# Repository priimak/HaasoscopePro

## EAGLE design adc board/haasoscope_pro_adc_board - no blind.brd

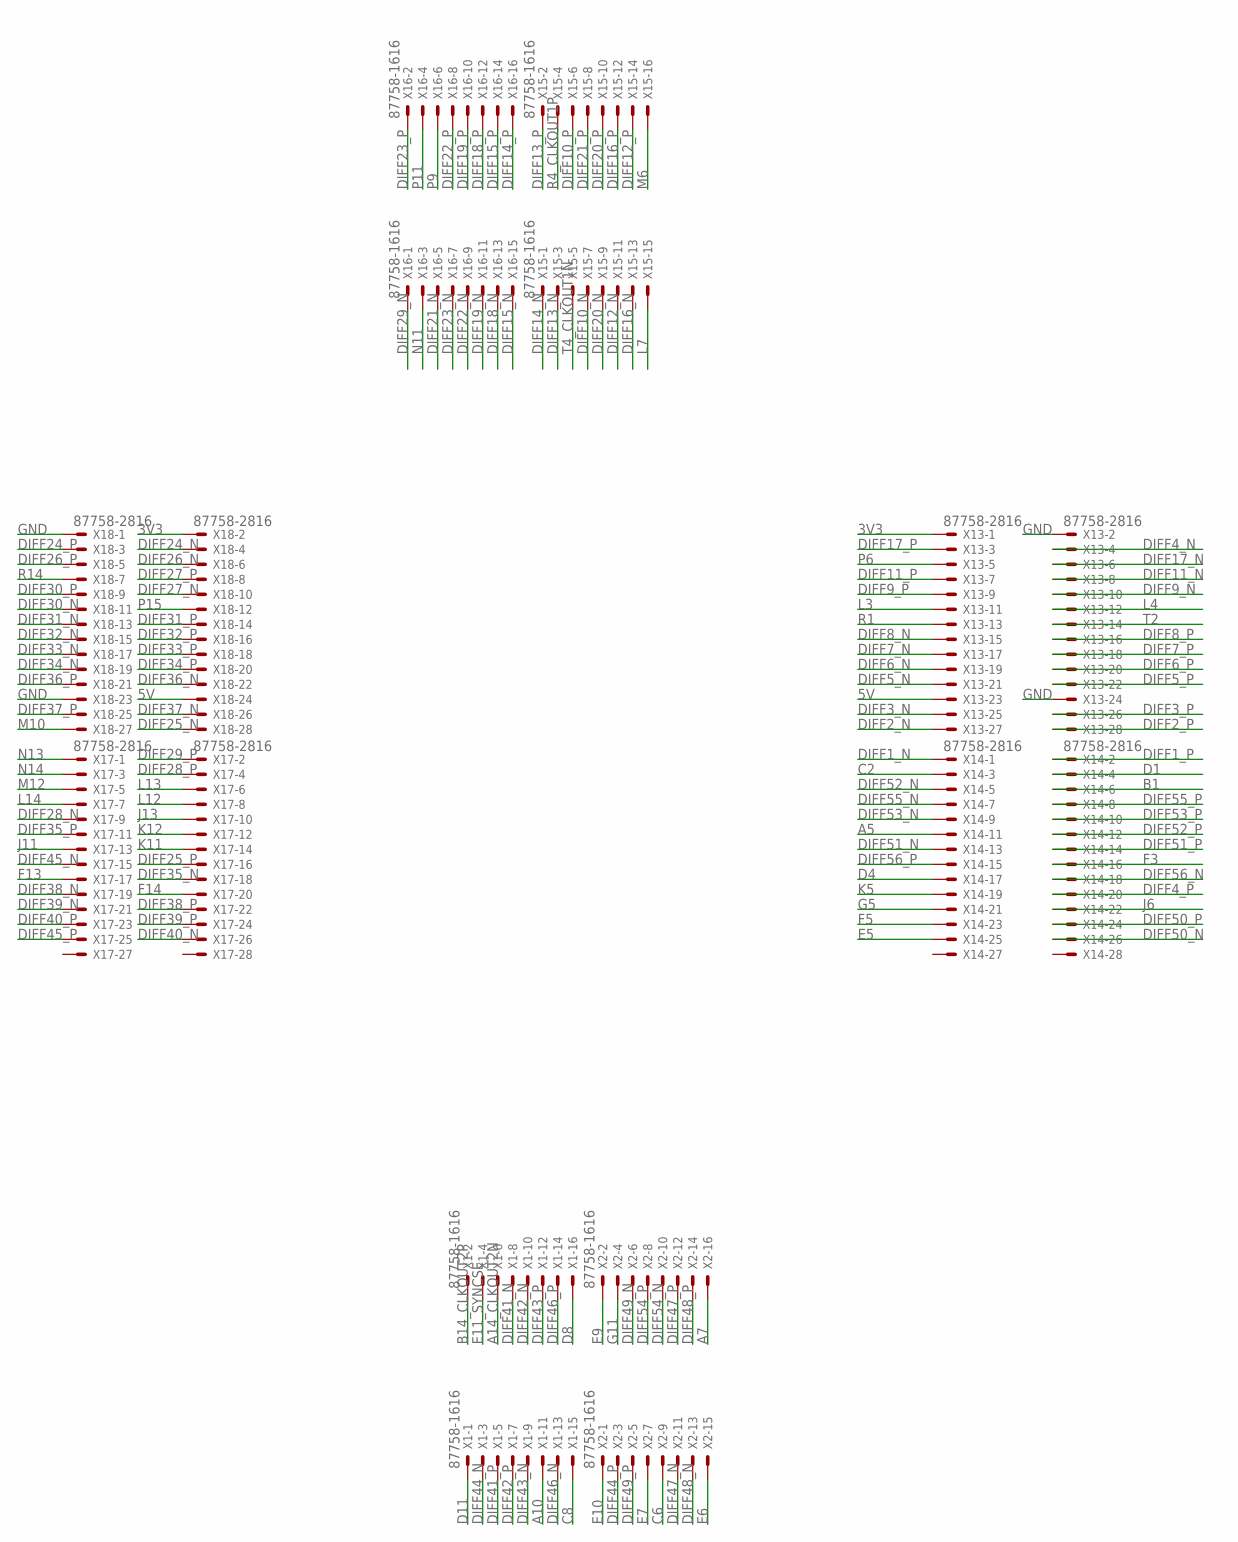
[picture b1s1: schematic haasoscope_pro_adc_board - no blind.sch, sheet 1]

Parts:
X1, X2, X15, X16: 87758-1616
X13, X14, X17, X18: 87758-2816

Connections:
3V3: X13.1, X18.2; also elsewhere on the board
5V: X13.23, X18.24; also elsewhere on the board
A5: X14.11; also elsewhere on the board
A7: X2.16; also elsewhere on the board
A10: X1.11; also elsewhere on the board
A14_CLKOUT2N: X1.6; also elsewhere on the board
B1: X14.6; also elsewhere on the board
B14_CLKOUT2P: X1.2; also elsewhere on the board
C2: X14.3; also elsewhere on the board
C6: X2.9; also elsewhere on the board
C8: X1.15; also elsewhere on the board
D1: X14.4; also elsewhere on the board
D4: X14.17; also elsewhere on the board
D8: X1.16; also elsewhere on the board
D11: X1.1; also elsewhere on the board
DIFF1_N: X14.1; also elsewhere on the board
DIFF1_P: X14.2; also elsewhere on the board
DIFF2_N: X13.27; also elsewhere on the board
DIFF2_P: X13.28; also elsewhere on the board
DIFF3_N: X13.25; also elsewhere on the board
DIFF3_P: X13.26; also elsewhere on the board
DIFF4_N: X13.4; also elsewhere on the board
DIFF4_P: X14.20; also elsewhere on the board
DIFF5_N: X13.21; also elsewhere on the board
DIFF5_P: X13.22; also elsewhere on the board
DIFF6_N: X13.19; also elsewhere on the board
DIFF6_P: X13.20; also elsewhere on the board
DIFF7_N: X13.17; also elsewhere on the board
DIFF7_P: X13.18; also elsewhere on the board
DIFF8_N: X13.15; also elsewhere on the board
DIFF8_P: X13.16; also elsewhere on the board
DIFF9_N: X13.10; also elsewhere on the board
DIFF9_P: X13.9; also elsewhere on the board
DIFF10_N: X15.7; also elsewhere on the board
DIFF10_P: X15.6; also elsewhere on the board
DIFF11_N: X13.8; also elsewhere on the board
DIFF11_P: X13.7; also elsewhere on the board
DIFF12_N: X15.11; also elsewhere on the board
DIFF12_P: X15.14; also elsewhere on the board
DIFF13_N: X15.3; also elsewhere on the board
DIFF13_P: X15.2; also elsewhere on the board
DIFF14_N: X15.1; also elsewhere on the board
DIFF14_P: X16.16; also elsewhere on the board
DIFF15_N: X16.15; also elsewhere on the board
DIFF15_P: X16.14; also elsewhere on the board
DIFF16_N: X15.13; also elsewhere on the board
DIFF16_P: X15.12; also elsewhere on the board
DIFF17_N: X13.6; also elsewhere on the board
DIFF17_P: X13.3; also elsewhere on the board
DIFF18_N: X16.13; also elsewhere on the board
DIFF18_P: X16.12; also elsewhere on the board
DIFF19_N: X16.11; also elsewhere on the board
DIFF19_P: X16.10; also elsewhere on the board
DIFF20_N: X15.9; also elsewhere on the board
DIFF20_P: X15.10; also elsewhere on the board
DIFF21_N: X16.5; also elsewhere on the board
DIFF21_P: X15.8; also elsewhere on the board
DIFF22_N: X16.9; also elsewhere on the board
DIFF22_P: X16.8; also elsewhere on the board
DIFF23_N: X16.7; also elsewhere on the board
DIFF23_P: X16.2; also elsewhere on the board
DIFF24_N: X18.4; also elsewhere on the board
DIFF24_P: X18.3; also elsewhere on the board
DIFF25_N: X18.28; also elsewhere on the board
DIFF25_P: X17.16; also elsewhere on the board
DIFF26_N: X18.6; also elsewhere on the board
DIFF26_P: X18.5; also elsewhere on the board
DIFF27_N: X18.10; also elsewhere on the board
DIFF27_P: X18.8; also elsewhere on the board
DIFF28_N: X17.9; also elsewhere on the board
DIFF28_P: X17.4; also elsewhere on the board
DIFF29_N: X16.1; also elsewhere on the board
DIFF29_P: X17.2; also elsewhere on the board
DIFF30_N: X18.11; also elsewhere on the board
DIFF30_P: X18.9; also elsewhere on the board
DIFF31_N: X18.13; also elsewhere on the board
DIFF31_P: X18.14; also elsewhere on the board
DIFF32_N: X18.15; also elsewhere on the board
DIFF32_P: X18.16; also elsewhere on the board
DIFF33_N: X18.17; also elsewhere on the board
DIFF33_P: X18.18; also elsewhere on the board
DIFF34_N: X18.19; also elsewhere on the board
DIFF34_P: X18.20; also elsewhere on the board
DIFF35_N: X17.18; also elsewhere on the board
DIFF35_P: X17.11; also elsewhere on the board
DIFF36_N: X18.22; also elsewhere on the board
DIFF36_P: X18.21; also elsewhere on the board
DIFF37_N: X18.26; also elsewhere on the board
DIFF37_P: X18.25; also elsewhere on the board
DIFF38_N: X17.19; also elsewhere on the board
DIFF38_P: X17.22; also elsewhere on the board
DIFF39_N: X17.21; also elsewhere on the board
DIFF39_P: X17.24; also elsewhere on the board
DIFF40_N: X17.26; also elsewhere on the board
DIFF40_P: X17.23; also elsewhere on the board
DIFF41_N: X1.8; also elsewhere on the board
DIFF41_P: X1.5; also elsewhere on the board
DIFF42_N: X1.10; also elsewhere on the board
DIFF42_P: X1.7; also elsewhere on the board
DIFF43_N: X1.9; also elsewhere on the board
DIFF43_P: X1.12; also elsewhere on the board
DIFF44_N: X1.3; also elsewhere on the board
DIFF44_P: X2.3; also elsewhere on the board
DIFF45_N: X17.15; also elsewhere on the board
DIFF45_P: X17.25; also elsewhere on the board
DIFF46_N: X1.13; also elsewhere on the board
DIFF46_P: X1.14; also elsewhere on the board
DIFF47_N: X2.11; also elsewhere on the board
DIFF47_P: X2.12; also elsewhere on the board
DIFF48_N: X2.13; also elsewhere on the board
DIFF48_P: X2.14; also elsewhere on the board
DIFF49_N: X2.6; also elsewhere on the board
DIFF49_P: X2.5; also elsewhere on the board
DIFF50_N: X14.26; also elsewhere on the board
DIFF50_P: X14.24; also elsewhere on the board
DIFF51_N: X14.13; also elsewhere on the board
DIFF51_P: X14.14; also elsewhere on the board
DIFF52_N: X14.5; also elsewhere on the board
DIFF52_P: X14.12; also elsewhere on the board
DIFF53_N: X14.9; also elsewhere on the board
DIFF53_P: X14.10; also elsewhere on the board
DIFF54_N: X2.10; also elsewhere on the board
DIFF54_P: X2.8; also elsewhere on the board
DIFF55_N: X14.7; also elsewhere on the board
DIFF55_P: X14.8; also elsewhere on the board
DIFF56_N: X14.18; also elsewhere on the board
DIFF56_P: X14.15; also elsewhere on the board
E5: X14.25; also elsewhere on the board
E6: X2.15; also elsewhere on the board
E7: X2.7; also elsewhere on the board
E9: X2.2; also elsewhere on the board
E10: X2.1; also elsewhere on the board
E11_SYNCSE: X1.4; also elsewhere on the board
F3: X14.16; also elsewhere on the board
F5: X14.23; also elsewhere on the board
F13: X17.17; also elsewhere on the board
F14: X17.20; also elsewhere on the board
G5: X14.21; also elsewhere on the board
G11: X2.4; also elsewhere on the board
GND: X13.2, X13.24, X18.1, X18.23; also elsewhere on the board
J6: X14.22; also elsewhere on the board
J11: X17.13; also elsewhere on the board
J13: X17.10; also elsewhere on the board
K5: X14.19; also elsewhere on the board
K11: X17.14; also elsewhere on the board
K12: X17.12; also elsewhere on the board
L3: X13.11; also elsewhere on the board
L4: X13.12; also elsewhere on the board
L7: X15.15; also elsewhere on the board
L12: X17.8; also elsewhere on the board
L13: X17.6; also elsewhere on the board
L14: X17.7; also elsewhere on the board
M6: X15.16; also elsewhere on the board
M10: X18.27; also elsewhere on the board
M12: X17.5; also elsewhere on the board
N11: X16.3; also elsewhere on the board
N13: X17.1; also elsewhere on the board
N14: X17.3; also elsewhere on the board
P6: X13.5; also elsewhere on the board
P9: X16.6; also elsewhere on the board
P11: X16.4; also elsewhere on the board
P15: X18.12; also elsewhere on the board
R1: X13.13; also elsewhere on the board
R4_CLKOUT1P: X15.4; also elsewhere on the board
R14: X18.7; also elsewhere on the board
T2: X13.14; also elsewhere on the board
T4_CLKOUT1N: X15.5; also elsewhere on the board

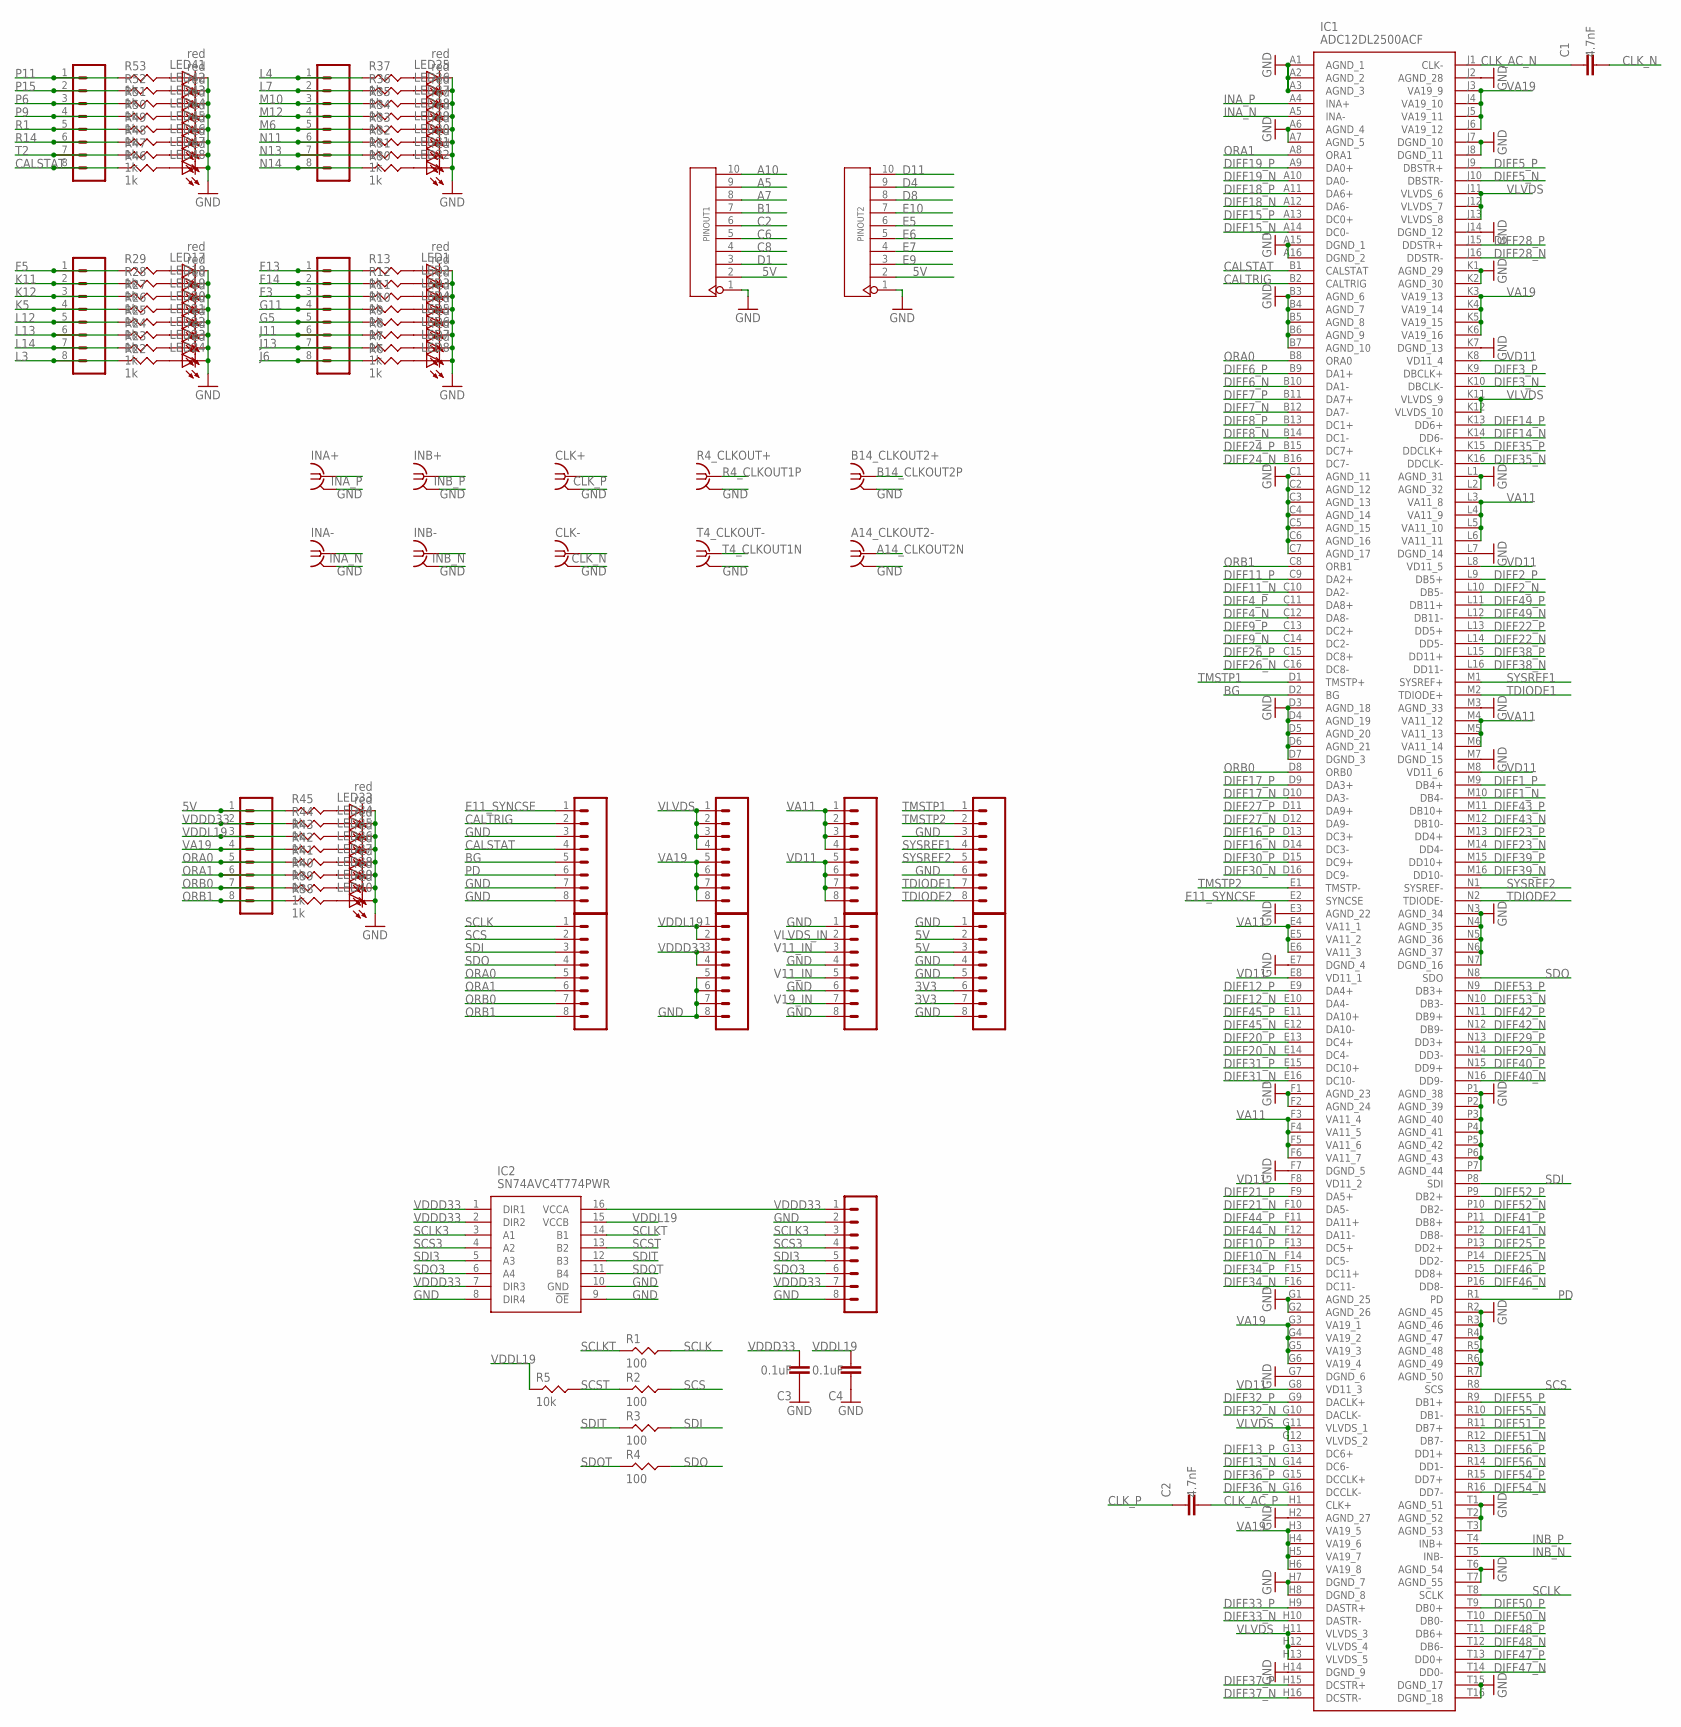
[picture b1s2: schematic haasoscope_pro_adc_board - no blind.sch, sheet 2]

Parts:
A14_CLKOUT2-: BU-SMB-V
B14_CLKOUT2+: BU-SMB-V
C1, C2: 4.7nF; RESC0402_N
C3, C4: 0.1uF; RESC0402_N
CLK+: BU-SMB-V
CLK-: BU-SMB-V
IC1: ADC12DL2500ACF; BGA256C100P16X16_1700X1700X331; MANUFACTURER_PART_NUMBER ADC12DL500ACF
IC2: SN74AVC4T774PWR; SOP65P640X120-16N
INA+: BU-SMB-V
INA-: BU-SMB-V
INB+: BU-SMB-V
INB-: BU-SMB-V
J1, J2, J3, J4, J5, J6, J7, J8, J10, J11, J12, J13, J16, J17: 8pin; 1X08
LED1, LED2, LED3, LED4, LED5, LED6, LED7, LED8, LED17, LED18, LED19, LED20, LED21, LED22, LED23, LED24, LED25, LED26, LED27, LED28, LED29, LED30, LED31, LED32, LED33, LED34, LED35, LED36, LED37, LED38, LED39, LED40, LED41, LED42, LED43, LED44, LED45, LED46, LED47, LED48: red; CHIP-LED0603
PINOUT1, PINOUT2: YELLOW-10P-2.54; H10-2.54
R1, R2, R3, R4: 100; RES-0402
R4_CLKOUT+: BU-SMB-V
R5: 10k; RES-0402
R6, R7, R8, R9, R10, R11, R12, R13, R22, R23, R24, R25, R26, R27, R28, R29, R30, R31, R32, R33, R34, R35, R36, R37, R38, R39, R40, R41, R42, R43, R44, R45, R46, R47, R48, R49, R50, R51, R52, R53: 1k; RES-0402
T4_CLKOUT-: BU-SMB-V

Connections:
3V3: J6.6, J6.7; also elsewhere on the board
5V: J6.2, J6.3, J12.1, PINOUT1.2, PINOUT2.2, R45.P$1; also elsewhere on the board
A5: PINOUT1.9; also elsewhere on the board
A7: PINOUT1.8; also elsewhere on the board
A10: PINOUT1.10; also elsewhere on the board
A14_CLKOUT2N: A14_CLKOUT2-.1; also elsewhere on the board
B1: PINOUT1.7; also elsewhere on the board
B14_CLKOUT2P: B14_CLKOUT2+.1; also elsewhere on the board
BG: IC1.D2 (BG), J17.5
C2: PINOUT1.6; also elsewhere on the board
C6: PINOUT1.5; also elsewhere on the board
C8: PINOUT1.4; also elsewhere on the board
CALSTAT: IC1.B1 (CALSTAT), J13.8, J17.4, R46.P$1
CALTRIG: IC1.B2 (CALTRIG), J17.2
CLK_AC_N: C1.1, IC1.J1 (CLK-)
CLK_AC_P: C2.2, IC1.H1 (CLK+)
CLK_N: C1.2, CLK-.1
CLK_P: C2.1, CLK+.1
D1: PINOUT1.3; also elsewhere on the board
D4: PINOUT2.9; also elsewhere on the board
D8: PINOUT2.8; also elsewhere on the board
D11: PINOUT2.10; also elsewhere on the board
DIFF1_N: IC1.M10 (DB4-); also elsewhere on the board
DIFF1_P: IC1.M9 (DB4+); also elsewhere on the board
DIFF2_N: IC1.L10 (DB5-); also elsewhere on the board
DIFF2_P: IC1.L9 (DB5+); also elsewhere on the board
DIFF3_N: IC1.K10 (DBCLK-); also elsewhere on the board
DIFF3_P: IC1.K9 (DBCLK+); also elsewhere on the board
DIFF4_N: IC1.C12 (DA8-); also elsewhere on the board
DIFF4_P: IC1.C11 (DA8+); also elsewhere on the board
DIFF5_N: IC1.J10 (DBSTR-); also elsewhere on the board
DIFF5_P: IC1.J9 (DBSTR+); also elsewhere on the board
DIFF6_N: IC1.B10 (DA1-); also elsewhere on the board
DIFF6_P: IC1.B9 (DA1+); also elsewhere on the board
DIFF7_N: IC1.B12 (DA7-); also elsewhere on the board
DIFF7_P: IC1.B11 (DA7+); also elsewhere on the board
DIFF8_N: IC1.B14 (DC1-); also elsewhere on the board
DIFF8_P: IC1.B13 (DC1+); also elsewhere on the board
DIFF9_N: IC1.C14 (DC2-); also elsewhere on the board
DIFF9_P: IC1.C13 (DC2+); also elsewhere on the board
DIFF10_N: IC1.F14 (DC5-); also elsewhere on the board
DIFF10_P: IC1.F13 (DC5+); also elsewhere on the board
DIFF11_N: IC1.C10 (DA2-); also elsewhere on the board
DIFF11_P: IC1.C9 (DA2+); also elsewhere on the board
DIFF12_N: IC1.E10 (DA4-); also elsewhere on the board
DIFF12_P: IC1.E9 (DA4+); also elsewhere on the board
DIFF13_N: IC1.G14 (DC6-); also elsewhere on the board
DIFF13_P: IC1.G13 (DC6+); also elsewhere on the board
DIFF14_N: IC1.K14 (DD6-); also elsewhere on the board
DIFF14_P: IC1.K13 (DD6+); also elsewhere on the board
DIFF15_N: IC1.A14 (DC0-); also elsewhere on the board
DIFF15_P: IC1.A13 (DC0+); also elsewhere on the board
DIFF16_N: IC1.D14 (DC3-); also elsewhere on the board
DIFF16_P: IC1.D13 (DC3+); also elsewhere on the board
DIFF17_N: IC1.D10 (DA3-); also elsewhere on the board
DIFF17_P: IC1.D9 (DA3+); also elsewhere on the board
DIFF18_N: IC1.A12 (DA6-); also elsewhere on the board
DIFF18_P: IC1.A11 (DA6+); also elsewhere on the board
DIFF19_N: IC1.A10 (DA0-); also elsewhere on the board
DIFF19_P: IC1.A9 (DA0+); also elsewhere on the board
DIFF20_N: IC1.E14 (DC4-); also elsewhere on the board
DIFF20_P: IC1.E13 (DC4+); also elsewhere on the board
DIFF21_N: IC1.F10 (DA5-); also elsewhere on the board
DIFF21_P: IC1.F9 (DA5+); also elsewhere on the board
DIFF22_N: IC1.L14 (DD5-); also elsewhere on the board
DIFF22_P: IC1.L13 (DD5+); also elsewhere on the board
DIFF23_N: IC1.M14 (DD4-); also elsewhere on the board
DIFF23_P: IC1.M13 (DD4+); also elsewhere on the board
DIFF24_N: IC1.B16 (DC7-); also elsewhere on the board
DIFF24_P: IC1.B15 (DC7+); also elsewhere on the board
DIFF25_N: IC1.P14 (DD2-); also elsewhere on the board
DIFF25_P: IC1.P13 (DD2+); also elsewhere on the board
DIFF26_N: IC1.C16 (DC8-); also elsewhere on the board
DIFF26_P: IC1.C15 (DC8+); also elsewhere on the board
DIFF27_N: IC1.D12 (DA9-); also elsewhere on the board
DIFF27_P: IC1.D11 (DA9+); also elsewhere on the board
DIFF28_N: IC1.J16 (DDSTR-); also elsewhere on the board
DIFF28_P: IC1.J15 (DDSTR+); also elsewhere on the board
DIFF29_N: IC1.N14 (DD3-); also elsewhere on the board
DIFF29_P: IC1.N13 (DD3+); also elsewhere on the board
DIFF30_N: IC1.D16 (DC9-); also elsewhere on the board
DIFF30_P: IC1.D15 (DC9+); also elsewhere on the board
DIFF31_N: IC1.E16 (DC10-); also elsewhere on the board
DIFF31_P: IC1.E15 (DC10+); also elsewhere on the board
DIFF32_N: IC1.G10 (DACLK-); also elsewhere on the board
DIFF32_P: IC1.G9 (DACLK+); also elsewhere on the board
DIFF33_N: IC1.H10 (DASTR-); also elsewhere on the board
DIFF33_P: IC1.H9 (DASTR+); also elsewhere on the board
DIFF34_N: IC1.F16 (DC11-); also elsewhere on the board
DIFF34_P: IC1.F15 (DC11+); also elsewhere on the board
DIFF35_N: IC1.K16 (DDCLK-); also elsewhere on the board
DIFF35_P: IC1.K15 (DDCLK+); also elsewhere on the board
DIFF36_N: IC1.G16 (DCCLK-); also elsewhere on the board
DIFF36_P: IC1.G15 (DCCLK+); also elsewhere on the board
DIFF37_N: IC1.H16 (DCSTR-); also elsewhere on the board
DIFF37_P: IC1.H15 (DCSTR+); also elsewhere on the board
DIFF38_N: IC1.L16 (DD11-); also elsewhere on the board
DIFF38_P: IC1.L15 (DD11+); also elsewhere on the board
DIFF39_N: IC1.M16 (DD10-); also elsewhere on the board
DIFF39_P: IC1.M15 (DD10+); also elsewhere on the board
DIFF40_N: IC1.N16 (DD9-); also elsewhere on the board
DIFF40_P: IC1.N15 (DD9+); also elsewhere on the board
DIFF41_N: IC1.P12 (DB8-); also elsewhere on the board
DIFF41_P: IC1.P11 (DB8+); also elsewhere on the board
DIFF42_N: IC1.N12 (DB9-); also elsewhere on the board
DIFF42_P: IC1.N11 (DB9+); also elsewhere on the board
DIFF43_N: IC1.M12 (DB10-); also elsewhere on the board
DIFF43_P: IC1.M11 (DB10+); also elsewhere on the board
DIFF44_N: IC1.F12 (DA11-); also elsewhere on the board
DIFF44_P: IC1.F11 (DA11+); also elsewhere on the board
DIFF45_N: IC1.E12 (DA10-); also elsewhere on the board
DIFF45_P: IC1.E11 (DA10+); also elsewhere on the board
DIFF46_N: IC1.P16 (DD8-); also elsewhere on the board
DIFF46_P: IC1.P15 (DD8+); also elsewhere on the board
DIFF47_N: IC1.T14 (DD0-); also elsewhere on the board
DIFF47_P: IC1.T13 (DD0+); also elsewhere on the board
DIFF48_N: IC1.T12 (DB6-); also elsewhere on the board
DIFF48_P: IC1.T11 (DB6+); also elsewhere on the board
DIFF49_N: IC1.L12 (DB11-); also elsewhere on the board
DIFF49_P: IC1.L11 (DB11+); also elsewhere on the board
DIFF50_N: IC1.T10 (DB0-); also elsewhere on the board
DIFF50_P: IC1.T9 (DB0+); also elsewhere on the board
DIFF51_N: IC1.R12 (DB7-); also elsewhere on the board
DIFF51_P: IC1.R11 (DB7+); also elsewhere on the board
DIFF52_N: IC1.P10 (DB2-); also elsewhere on the board
DIFF52_P: IC1.P9 (DB2+); also elsewhere on the board
DIFF53_N: IC1.N10 (DB3-); also elsewhere on the board
DIFF53_P: IC1.N9 (DB3+); also elsewhere on the board
DIFF54_N: IC1.R16 (DD7-); also elsewhere on the board
DIFF54_P: IC1.R15 (DD7+); also elsewhere on the board
DIFF55_N: IC1.R10 (DB1-); also elsewhere on the board
DIFF55_P: IC1.R9 (DB1+); also elsewhere on the board
DIFF56_N: IC1.R14 (DD1-); also elsewhere on the board
DIFF56_P: IC1.R13 (DD1+); also elsewhere on the board
E5: PINOUT2.6; also elsewhere on the board
E6: PINOUT2.5; also elsewhere on the board
E7: PINOUT2.4; also elsewhere on the board
E9: PINOUT2.3; also elsewhere on the board
E10: PINOUT2.7; also elsewhere on the board
E11_SYNCSE: IC1.E2 (SYNCSE), J17.1; also elsewhere on the board
F3: J8.3, R11.P$1; also elsewhere on the board
F5: J10.1, R29.P$1; also elsewhere on the board
F13: J8.1, R13.P$1; also elsewhere on the board
F14: J8.2, R12.P$1; also elsewhere on the board
G5: J8.5, R9.P$1; also elsewhere on the board
G11: J8.4, R10.P$1; also elsewhere on the board
GND: A14_CLKOUT2-.2, A14_CLKOUT2-.3 (2), A14_CLKOUT2-.4 (2), A14_CLKOUT2-.5 (2), B14_CLKOUT2+.2, B14_CLKOUT2+.3 (2), B14_CLKOUT2+.4 (2), B14_CLKOUT2+.5 (2), C3.1, C4.1, CLK+.2, CLK+.3 (2), CLK+.4 (2), CLK+.5 (2), CLK-.2, CLK-.3 (2), CLK-.4 (2), CLK-.5 (2), IC1.A1 (AGND_1), IC1.A2 (AGND_2), IC1.A3 (AGND_3), IC1.A6 (AGND_4), IC1.A7 (AGND_5), IC1.A15 (DGND_1), IC1.A16 (DGND_2), IC1.B3 (AGND_6), IC1.B4 (AGND_7), IC1.B5 (AGND_8), IC1.B6 (AGND_9), IC1.B7 (AGND_10), IC1.C1 (AGND_11), IC1.C2 (AGND_12), IC1.C3 (AGND_13), IC1.C4 (AGND_14), IC1.C5 (AGND_15), IC1.C6 (AGND_16), IC1.C7 (AGND_17), IC1.D3 (AGND_18), IC1.D4 (AGND_19), IC1.D5 (AGND_20), IC1.D6 (AGND_21), IC1.D7 (DGND_3), IC1.E3 (AGND_22), IC1.E7 (DGND_4), IC1.F1 (AGND_23), IC1.F2 (AGND_24), IC1.F7 (DGND_5), IC1.G1 (AGND_25), IC1.G2 (AGND_26), IC1.G7 (DGND_6), IC1.H2 (AGND_27), IC1.H7 (DGND_7), IC1.H8 (DGND_8), IC1.H14 (DGND_9), IC1.J2 (AGND_28), IC1.J7 (DGND_10), IC1.J8 (DGND_11), IC1.J14 (DGND_12), IC1.K1 (AGND_29), IC1.K2 (AGND_30), IC1.K7 (DGND_13), IC1.L1 (AGND_31), IC1.L2 (AGND_32), IC1.L7 (DGND_14), IC1.M3 (AGND_33), IC1.M7 (DGND_15), IC1.N3 (AGND_34), IC1.N4 (AGND_35), IC1.N5 (AGND_36), IC1.N6 (AGND_37), IC1.N7 (DGND_16), IC1.P1 (AGND_38), IC1.P2 (AGND_39), IC1.P3 (AGND_40), IC1.P4 (AGND_41), IC1.P5 (AGND_42), IC1.P6 (AGND_43), IC1.P7 (AGND_44), IC1.R2 (AGND_45), IC1.R3 (AGND_46), IC1.R4 (AGND_47), IC1.R5 (AGND_48), IC1.R6 (AGND_49), IC1.R7 (AGND_50), IC1.T1 (AGND_51), IC1.T2 (AGND_52), IC1.T3 (AGND_53), IC1.T6 (AGND_54), IC1.T7 (AGND_55), IC1.T15 (DGND_17), IC1.T16 (DGND_18), IC2.8 (DIR4), IC2.9 (!OE), IC2.10 (GND), INA+.2, INA+.3 (2), INA+.4 (2), INA+.5 (2), INA-.2, INA-.3 (2), INA-.4 (2), INA-.5 (2), INB+.2, INB+.3 (2), INB+.4 (2), INB+.5 (2), INB-.2, INB-.3 (2), INB-.4 (2), INB-.5 (2), J2.5, J2.6, J2.7, J2.8, J4.2, J4.8, J5.1, J5.4, J5.6, J5.8, J6.1, J6.4, J6.5, J6.8, J7.3, J7.6, J17.3, J17.7, J17.8, LED1.C, LED2.C, LED3.C, LED4.C, LED5.C, LED6.C, LED7.C, LED8.C, LED17.C, LED18.C, LED19.C, LED20.C, LED21.C, LED22.C, LED23.C, LED24.C, LED25.C, LED26.C, LED27.C, LED28.C, LED29.C, LED30.C, LED31.C, LED32.C, LED33.C, LED34.C, LED35.C, LED36.C, LED37.C, LED38.C, LED39.C, LED40.C, LED41.C, LED42.C, LED43.C, LED44.C, LED45.C, LED46.C, LED47.C, LED48.C, PINOUT1.1, PINOUT2.1, R4_CLKOUT+.2, R4_CLKOUT+.3 (2), R4_CLKOUT+.4 (2), R4_CLKOUT+.5 (2), T4_CLKOUT-.2, T4_CLKOUT-.3 (2), T4_CLKOUT-.4 (2), T4_CLKOUT-.5 (2); also elsewhere on the board
INA_N: IC1.A5 (INA-), INA-.1
INA_P: IC1.A4 (INA+), INA+.1
INB_N: IC1.T5 (INB-), INB-.1
INB_P: IC1.T4 (INB+), INB+.1
J6: J8.8, R6.P$1; also elsewhere on the board
J11: J8.6, R8.P$1; also elsewhere on the board
J13: J8.7, R7.P$1; also elsewhere on the board
K5: J10.4, R26.P$1; also elsewhere on the board
K11: J10.2, R28.P$1; also elsewhere on the board
K12: J10.3, R27.P$1; also elsewhere on the board
L3: J10.8, R22.P$1; also elsewhere on the board
L4: J11.1, R37.P$1; also elsewhere on the board
L7: J11.2, R36.P$1; also elsewhere on the board
L12: J10.5, R25.P$1; also elsewhere on the board
L13: J10.6, R24.P$1; also elsewhere on the board
L14: J10.7, R23.P$1; also elsewhere on the board
M6: J11.5, R33.P$1; also elsewhere on the board
M10: J11.3, R35.P$1; also elsewhere on the board
M12: J11.4, R34.P$1; also elsewhere on the board
N11: J11.6, R32.P$1; also elsewhere on the board
N13: J11.7, R31.P$1; also elsewhere on the board
N14: J11.8, R30.P$1; also elsewhere on the board
unnamed: LED1.A, R13.P$2
unnamed: LED2.A, R12.P$2
unnamed: LED3.A, R11.P$2
unnamed: LED4.A, R10.P$2
unnamed: LED5.A, R9.P$2
unnamed: LED6.A, R8.P$2
unnamed: LED7.A, R7.P$2
unnamed: LED8.A, R6.P$2
unnamed: LED17.A, R29.P$2
unnamed: LED18.A, R28.P$2
unnamed: LED19.A, R27.P$2
unnamed: LED20.A, R26.P$2
unnamed: LED21.A, R25.P$2
unnamed: LED22.A, R24.P$2
unnamed: LED23.A, R23.P$2
unnamed: LED24.A, R22.P$2
unnamed: LED25.A, R37.P$2
unnamed: LED26.A, R36.P$2
unnamed: LED27.A, R35.P$2
unnamed: LED28.A, R34.P$2
unnamed: LED29.A, R33.P$2
unnamed: LED30.A, R32.P$2
unnamed: LED31.A, R31.P$2
unnamed: LED32.A, R30.P$2
unnamed: LED33.A, R45.P$2
unnamed: LED34.A, R44.P$2
unnamed: LED35.A, R43.P$2
unnamed: LED36.A, R42.P$2
unnamed: LED37.A, R41.P$2
unnamed: LED38.A, R40.P$2
unnamed: LED39.A, R39.P$2
unnamed: LED40.A, R38.P$2
unnamed: LED41.A, R53.P$2
unnamed: LED42.A, R52.P$2
unnamed: LED43.A, R51.P$2
unnamed: LED44.A, R50.P$2
unnamed: LED45.A, R49.P$2
unnamed: LED46.A, R48.P$2
unnamed: LED47.A, R47.P$2
unnamed: LED48.A, R46.P$2
ORA0: IC1.B8 (ORA0), J12.5, J16.5, R41.P$1
ORA1: IC1.A8 (ORA1), J12.6, J16.6, R40.P$1
ORB0: IC1.D8 (ORB0), J12.7, J16.7, R39.P$1
ORB1: IC1.C8 (ORB1), J12.8, J16.8, R38.P$1
P6: J13.3, R51.P$1; also elsewhere on the board
P9: J13.4, R50.P$1; also elsewhere on the board
P11: J13.1, R53.P$1; also elsewhere on the board
P15: J13.2, R52.P$1; also elsewhere on the board
PD: IC1.R1 (PD), J17.6
R1: J13.5, R49.P$1; also elsewhere on the board
R4_CLKOUT1P: R4_CLKOUT+.1; also elsewhere on the board
R14: J13.6, R48.P$1; also elsewhere on the board
SCLK: IC1.T8 (SCLK), J16.1, R1.P$2
SCLK3: IC2.3 (A1), J4.3
SCLKT: IC2.14 (B1), R1.P$1
SCS: IC1.R8 (SCS), J16.2, R2.P$2
SCS3: IC2.4 (A2), J4.4
SCST: IC2.13 (B2), R2.P$1, R5.P$2
SDI: IC1.P8 (SDI), J16.3, R3.P$2
SDI3: IC2.5 (A3), J4.5
SDIT: IC2.12 (B3), R3.P$1
SDO: IC1.N8 (SDO), J16.4, R4.P$2
SDO3: IC2.6 (A4), J4.6
SDOT: IC2.11 (B4), R4.P$1
SYSREF1: IC1.M1 (SYSREF+), J7.4
SYSREF2: IC1.N1 (SYSREF-), J7.5
T2: J13.7, R47.P$1; also elsewhere on the board
T4_CLKOUT1N: T4_CLKOUT-.1; also elsewhere on the board
TDIODE1: IC1.M2 (TDIODE+), J7.7
TDIODE2: IC1.N2 (TDIODE-), J7.8
TMSTP1: IC1.D1 (TMSTP+), J7.1
TMSTP2: IC1.E1 (TMSTP-), J7.2
V11_IN: J5.3, J5.5; also elsewhere on the board
V19_IN: J5.7; also elsewhere on the board
VA11: IC1.E4 (VA11_1), IC1.E5 (VA11_2), IC1.E6 (VA11_3), IC1.F3 (VA11_4), IC1.F4 (VA11_5), IC1.F5 (VA11_6), IC1.F6 (VA11_7), IC1.L3 (VA11_8), IC1.L4 (VA11_9), IC1.L5 (VA11_10), IC1.L6 (VA11_11), IC1.M4 (VA11_12), IC1.M5 (VA11_13), IC1.M6 (VA11_14), J3.1, J3.2, J3.3, J3.4; also elsewhere on the board
VA19: IC1.G3 (VA19_1), IC1.G4 (VA19_2), IC1.G5 (VA19_3), IC1.G6 (VA19_4), IC1.H3 (VA19_5), IC1.H4 (VA19_6), IC1.H5 (VA19_7), IC1.H6 (VA19_8), IC1.J3 (VA19_9), IC1.J4 (VA19_10), IC1.J5 (VA19_11), IC1.J6 (VA19_12), IC1.K3 (VA19_13), IC1.K4 (VA19_14), IC1.K5 (VA19_15), IC1.K6 (VA19_16), J1.5, J1.6, J1.7, J1.8, J12.4, R42.P$1; also elsewhere on the board
VD11: IC1.E8 (VD11_1), IC1.F8 (VD11_2), IC1.G8 (VD11_3), IC1.K8 (VD11_4), IC1.L8 (VD11_5), IC1.M8 (VD11_6), J3.5, J3.6, J3.7, J3.8; also elsewhere on the board
VDDD33: C3.2, IC2.1 (DIR1), IC2.2 (DIR2), IC2.7 (DIR3), IC2.16 (VCCA), J2.3, J2.4, J4.1, J4.7, J12.2, R44.P$1
VDDL19: C4.2, IC2.15 (VCCB), J2.1, J2.2, J12.3, R5.P$1, R43.P$1; also elsewhere on the board
VLVDS: IC1.G11 (VLVDS_1), IC1.G12 (VLVDS_2), IC1.H11 (VLVDS_3), IC1.H12 (VLVDS_4), IC1.H13 (VLVDS_5), IC1.J11 (VLVDS_6), IC1.J12 (VLVDS_7), IC1.J13 (VLVDS_8), IC1.K11 (VLVDS_9), IC1.K12 (VLVDS_10), J1.1, J1.2, J1.3, J1.4; also elsewhere on the board
VLVDS_IN: J5.2; also elsewhere on the board

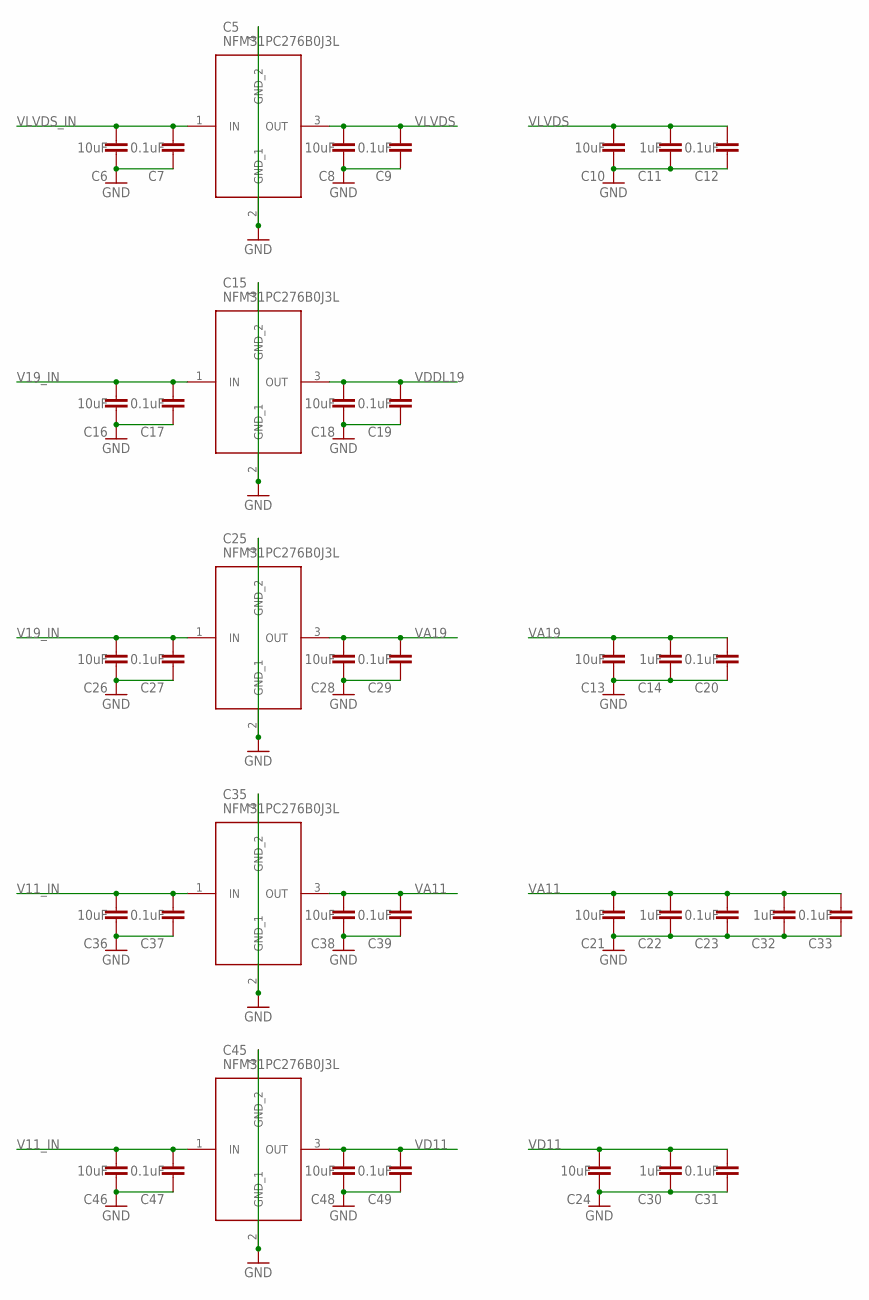
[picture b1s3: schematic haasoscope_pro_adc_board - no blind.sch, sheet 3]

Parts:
C5, C15, C25, C35, C45: NFM31PC276B0J3L; NFM31HK103R1H3L
C6, C8, C10, C13, C16, C18, C21, C24, C26, C28, C36, C38, C46, C48: 10uF; RESC0805_N
C7, C9, C12, C17, C19, C20, C23, C27, C29, C31, C33, C37, C39, C47, C49: 0.1uF; RESC0402_N
C11, C14, C22, C30, C32: 1uF; RESC0402_N

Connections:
GND: C5.2 (GND_1), C5.4 (GND_2), C6.1, C7.1, C8.1, C9.1, C10.1, C11.1, C12.1, C13.1, C14.1, C15.2 (GND_1), C15.4 (GND_2), C16.1, C17.1, C18.1, C19.1, C20.1, C21.1, C22.1, C23.1, C24.1, C25.2 (GND_1), C25.4 (GND_2), C26.1, C27.1, C28.1, C29.1, C30.1, C31.1, C32.1, C33.1, C35.2 (GND_1), C35.4 (GND_2), C36.1, C37.1, C38.1, C39.1, C45.2 (GND_1), C45.4 (GND_2), C46.1, C47.1, C48.1, C49.1; also elsewhere on the board
V11_IN: C35.1 (IN), C36.2, C37.2, C45.1 (IN), C46.2, C47.2; also elsewhere on the board
V19_IN: C15.1 (IN), C16.2, C17.2, C25.1 (IN), C26.2, C27.2; also elsewhere on the board
VA11: C21.2, C22.2, C23.2, C32.2, C33.2, C35.3 (OUT), C38.2, C39.2; also elsewhere on the board
VA19: C13.2, C14.2, C20.2, C25.3 (OUT), C28.2, C29.2; also elsewhere on the board
VD11: C24.2, C30.2, C31.2, C45.3 (OUT), C48.2, C49.2; also elsewhere on the board
VDDL19: C15.3 (OUT), C18.2, C19.2; also elsewhere on the board
VLVDS: C5.3 (OUT), C8.2, C9.2, C10.2, C11.2, C12.2; also elsewhere on the board
VLVDS_IN: C5.1 (IN), C6.2, C7.2; also elsewhere on the board

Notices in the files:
parts and their libraries:
SparkFun-Connectors: Licensing: Creative Commons ShareAlike 4.0 International - https://creativecommons.org/licenses/by-sa/4.0
microbuilder: This work is placed in the public domain, and may be freely used for commercial and non-commercial work with the following conditions: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
